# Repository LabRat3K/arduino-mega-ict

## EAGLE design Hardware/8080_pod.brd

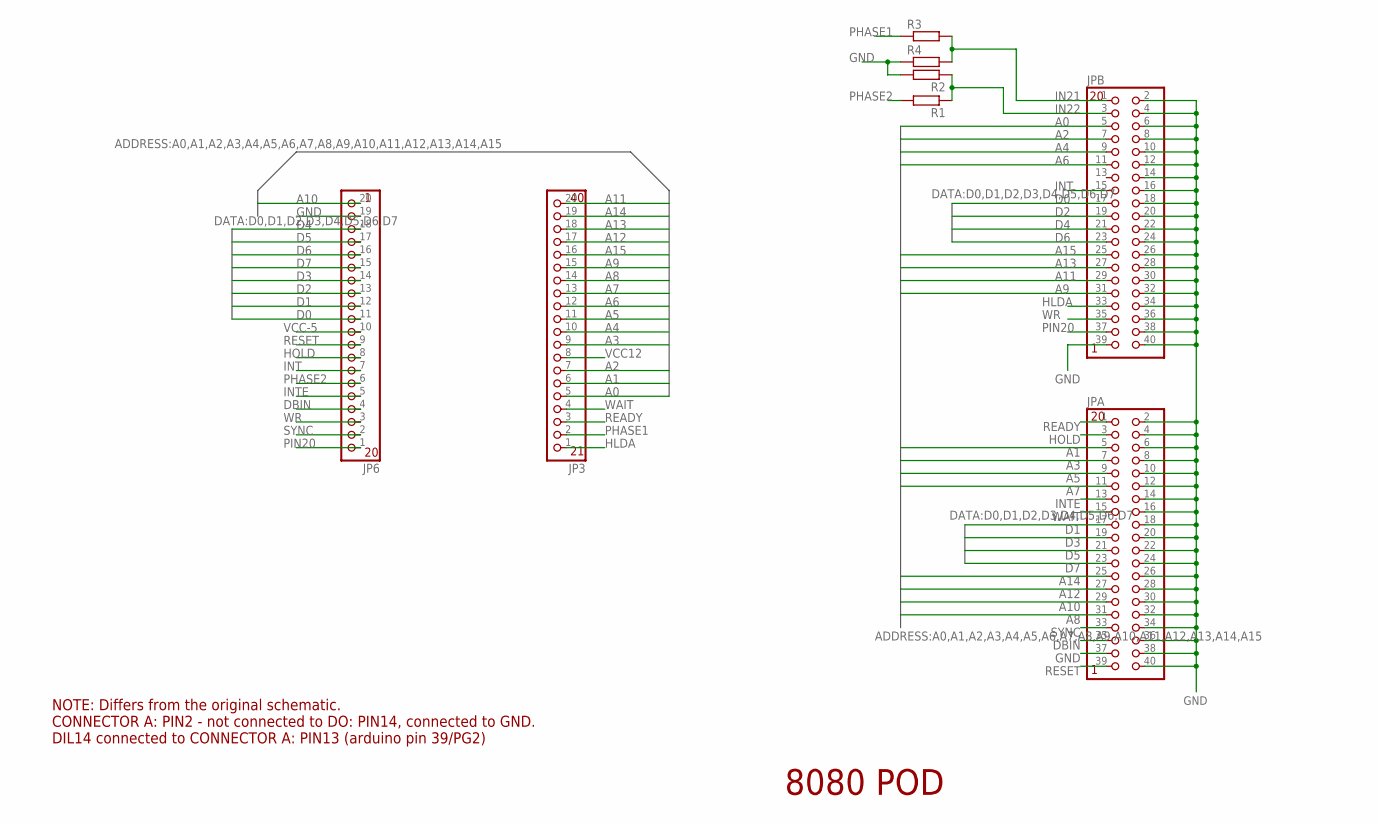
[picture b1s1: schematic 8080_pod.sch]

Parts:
JP3, JP6: PINHD-1X20-BIG; 1X20-BIG
JPA: PINHD-2X20-BIG; 2X20-BIG
JPB: PINHD-2X20-BIG; 2X20-BIG
R1, R2, R3, R4: R-EU_0207/10; 0207/10

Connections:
A0: JP3.5, JPB.5
A1: JP3.6, JPA.5
A2: JP3.7, JPB.7
A3: JP3.9, JPA.7
A4: JP3.10, JPB.9
A5: JP3.11, JPA.9
A6: JP3.12, JPB.11
A7: JP3.13, JPA.11
A8: JP3.14, JPA.31
A9: JP3.15, JPB.31
A10: JP6.20, JPA.29
A11: JP3.20, JPB.29
A12: JP3.17, JPA.27
A13: JP3.18, JPB.27
A14: JP3.19, JPA.25
A15: JP3.16, JPB.25
D0: JP6.11, JPB.17
D1: JP6.12, JPA.17
D2: JP6.13, JPB.19
D3: JP6.14, JPA.19
D4: JP6.18, JPB.21
D5: JP6.17, JPA.21
D6: JP6.16, JPB.23
D7: JP6.15, JPA.23
DBIN: JP6.4, JPA.35
GND: JP6.19, JPA.2, JPA.4, JPA.6, JPA.8, JPA.10, JPA.12, JPA.14, JPA.16, JPA.18, JPA.20, JPA.22, JPA.24, JPA.26, JPA.28, JPA.30, JPA.32, JPA.34, JPA.36, JPA.37, JPA.38, JPA.40, JPB.2, JPB.4, JPB.6, JPB.8, JPB.10, JPB.12, JPB.14, JPB.16, JPB.18, JPB.20, JPB.22, JPB.24, JPB.26, JPB.28, JPB.30, JPB.32, JPB.34, JPB.36, JPB.38, JPB.39, JPB.40, R2.2, R4.1
HLDA: JP3.1, JPB.33
HOLD: JP6.8, JPA.3
IN21: JPB.1, R3.2, R4.2
IN22: JPB.3, R1.1, R2.1
INT: JP6.7, JPB.15
INTE: JP6.5, JPA.13
PHASE1: JP3.2, R3.1
PHASE2: JP6.6, R1.2
PIN20: JP6.1, JPB.37
READY: JP3.3, JPA.1
RESET: JP6.9, JPA.39
SYNC: JP6.2, JPA.33
VCC12: JP3.8
VCC-5: JP6.10
WAIT: JP3.4, JPA.15
WR: JP6.3, JPB.35

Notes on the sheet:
8080 POD
NOTE: Differs from the original schematic. CONNECTOR A: PIN2 - not connected to DO: PIN14, connected to GND. DIL14 connected to CONNECTOR A: PIN13 (arduino pin 39/PG2)

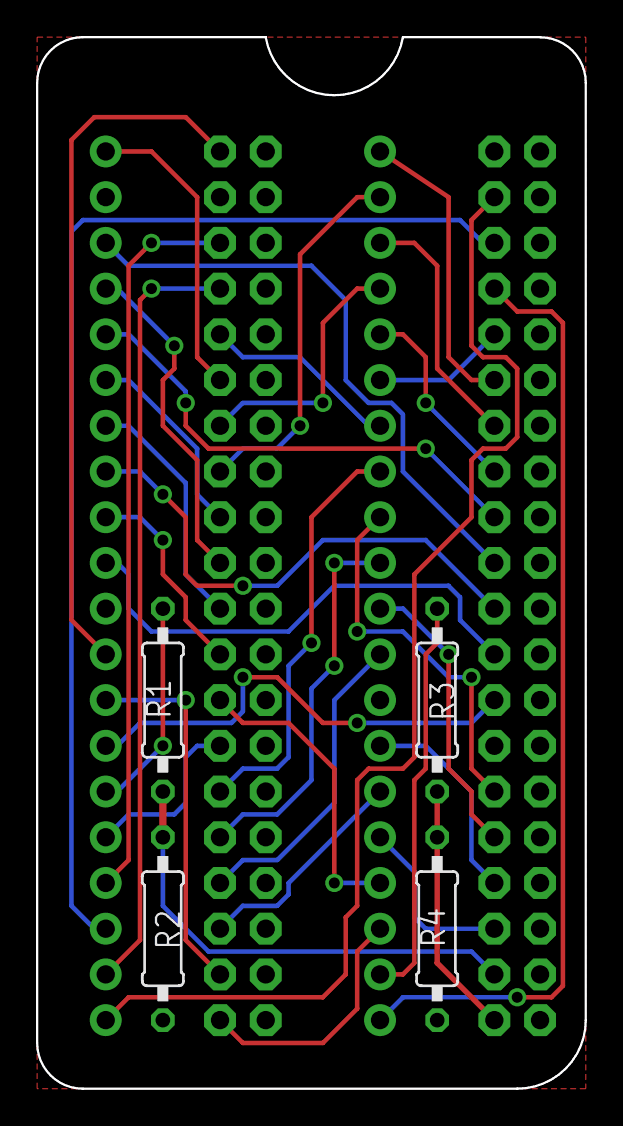
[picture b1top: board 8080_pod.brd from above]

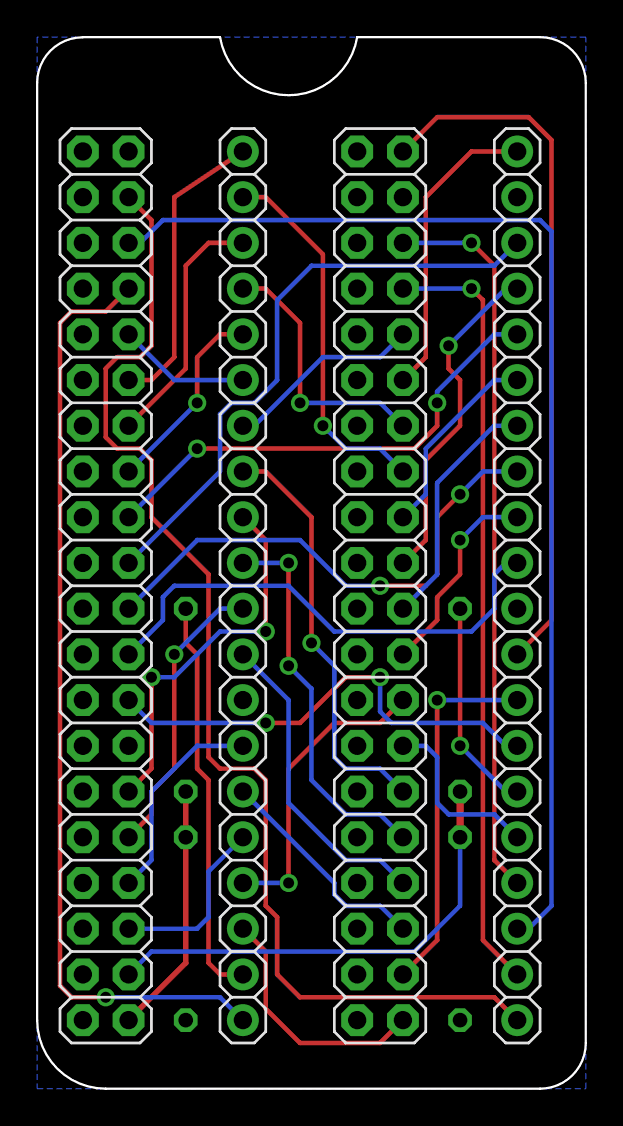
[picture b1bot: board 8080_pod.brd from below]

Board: 2 copper layers, 30.5 x 58.4 mm, 8 parts (4 on the bottom side), 40 nets.

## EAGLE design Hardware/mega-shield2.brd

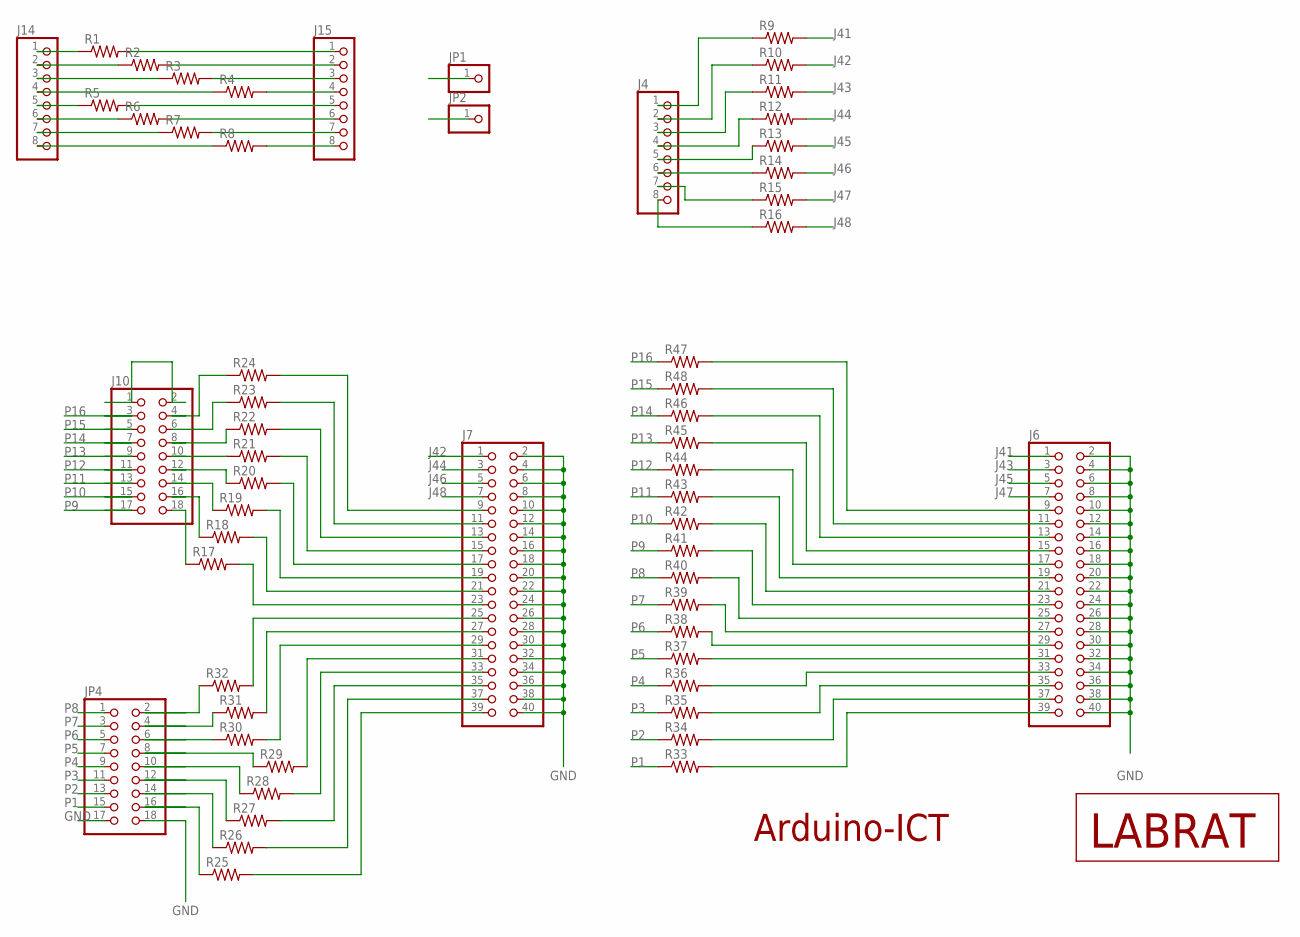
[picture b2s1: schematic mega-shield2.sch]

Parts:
J4, J14, J15: PINHD-1X8BIG; 1X08-BIG
J6, J7: PINHD-2X20; 2X20
J10: PINHD-2X9-BIG; 2X09-BIG
JP1, JP2: PINHD-1X1; 1X01
JP4: PINHD-2X9-BIG; 2X09-BIG
R1, R2, R3, R4, R5, R6, R7, R8, R9, R10, R11, R12, R13, R14, R15, R16, R17, R18, R19, R20, R21, R22, R23, R24, R25, R26, R27, R28, R29, R30, R31, R32, R33, R34, R35, R36, R37, R38, R39, R40, R41, R42, R43, R44, R45, R46, R47, R48: R-US_0204/5; 0204/5
U$1: LOGOLABRAT; LOGO

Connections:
GND: J6.2, J6.4, J6.6, J6.8, J6.10, J6.12, J6.14, J6.16, J6.18, J6.20, J6.22, J6.24, J6.26, J6.28, J6.30, J6.32, J6.34, J6.36, J6.38, J6.40, J7.2, J7.4, J7.6, J7.8, J7.10, J7.12, J7.14, J7.16, J7.18, J7.20, J7.22, J7.24, J7.26, J7.28, J7.30, J7.32, J7.34, J7.36, J7.38, J7.40, JP1.1, JP2.1, JP4.17, JP4.18
J41: J6.1, R9.2
J42: J7.1, R10.2
J43: J6.3, R11.2
J44: J7.3, R12.2
J45: J6.5, R13.2
J46: J7.5, R14.2
J47: J6.7, R15.2
J48: J7.7, R16.2
unnamed: J14.1, R1.1
unnamed: J15.1, R1.2
unnamed: J14.2, R2.1
unnamed: J14.3, R3.1
unnamed: J14.4, R4.1
unnamed: J14.5, R5.1
unnamed: J14.6, R6.1
unnamed: J14.7, R7.1
unnamed: J14.8, R8.1
unnamed: J15.2, R2.2
unnamed: J15.3, R3.2
unnamed: J15.4, R4.2
unnamed: J15.5, R5.2
unnamed: J15.6, R6.2
unnamed: J15.7, R7.2
unnamed: J15.8, R8.2
unnamed: JP4.16, R25.1
unnamed: J7.39, R25.2
unnamed: JP4.14, R26.1
unnamed: JP4.12, R27.1
unnamed: JP4.10, R28.1
unnamed: J7.37, R26.2
unnamed: J7.35, R27.2
unnamed: J7.33, R28.2
unnamed: JP4.8, R29.1
unnamed: JP4.6, R30.1
unnamed: JP4.4, R31.1
unnamed: JP4.2, R32.1
unnamed: J7.31, R29.2
unnamed: J7.29, R30.2
unnamed: J7.27, R31.2
unnamed: J7.25, R32.2
unnamed: J7.23, R17.2
unnamed: J7.21, R18.2
unnamed: J7.19, R19.2
unnamed: J7.17, R20.2
unnamed: J10.18, R17.1
unnamed: J10.16, R18.1
unnamed: J10.14, R19.1
unnamed: J10.12, R20.1
unnamed: J10.10, R21.1
unnamed: J10.8, R22.1
unnamed: J10.6, R23.1
unnamed: J10.4, R24.1
unnamed: J7.15, R21.2
unnamed: J7.13, R22.2
unnamed: J7.11, R23.2
unnamed: J7.9, R24.2
unnamed: J10.1, J10.2
unnamed: J4.8, R16.1
unnamed: J4.7, R15.1
unnamed: J4.6, R14.1
unnamed: J4.5, R13.1
unnamed: J4.4, R12.1
unnamed: J4.3, R11.1
unnamed: J4.2, R10.1
unnamed: J4.1, R9.1
unnamed: J6.39, R33.2
unnamed: J6.37, R34.2
unnamed: J6.35, R35.2
unnamed: J6.33, R36.2
unnamed: J6.31, R37.2
unnamed: J6.29, R38.2
unnamed: J6.27, R39.2
unnamed: J6.25, R40.2
unnamed: J6.23, R41.2
unnamed: J6.21, R42.2
unnamed: J6.19, R43.2
unnamed: J6.17, R44.2
unnamed: J6.15, R45.2
unnamed: J6.13, R46.2
unnamed: J6.11, R48.2
unnamed: J6.9, R47.2
P1: JP4.15, R33.1
P2: JP4.13, R34.1
P3: JP4.11, R35.1
P4: JP4.9, R36.1
P5: JP4.7, R37.1
P6: JP4.5, R38.1
P7: JP4.3, R39.1
P8: JP4.1, R40.1
P9: J10.17, R41.1
P10: J10.15, R42.1
P11: J10.13, R43.1
P12: J10.11, R44.1
P13: J10.9, R45.1
P14: J10.7, R46.1
P15: J10.5, R48.1
P16: J10.3, R47.1

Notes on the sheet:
Arduino-ICT

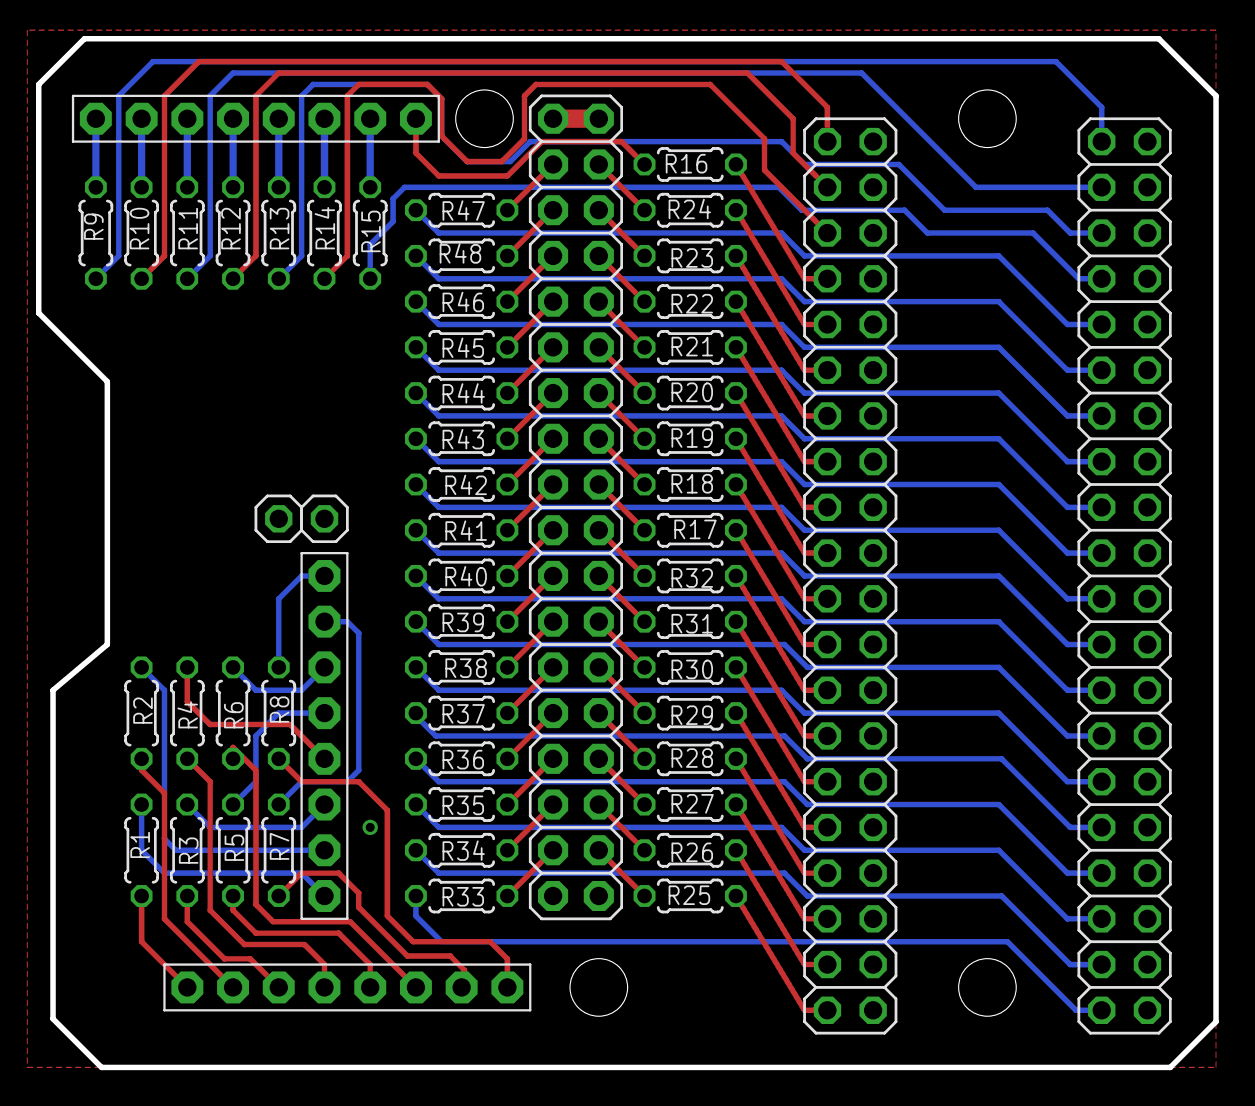
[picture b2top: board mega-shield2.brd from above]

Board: 2 copper layers, 65.4 x 57.1 mm, 58 parts (0 on the bottom side), 98 nets.

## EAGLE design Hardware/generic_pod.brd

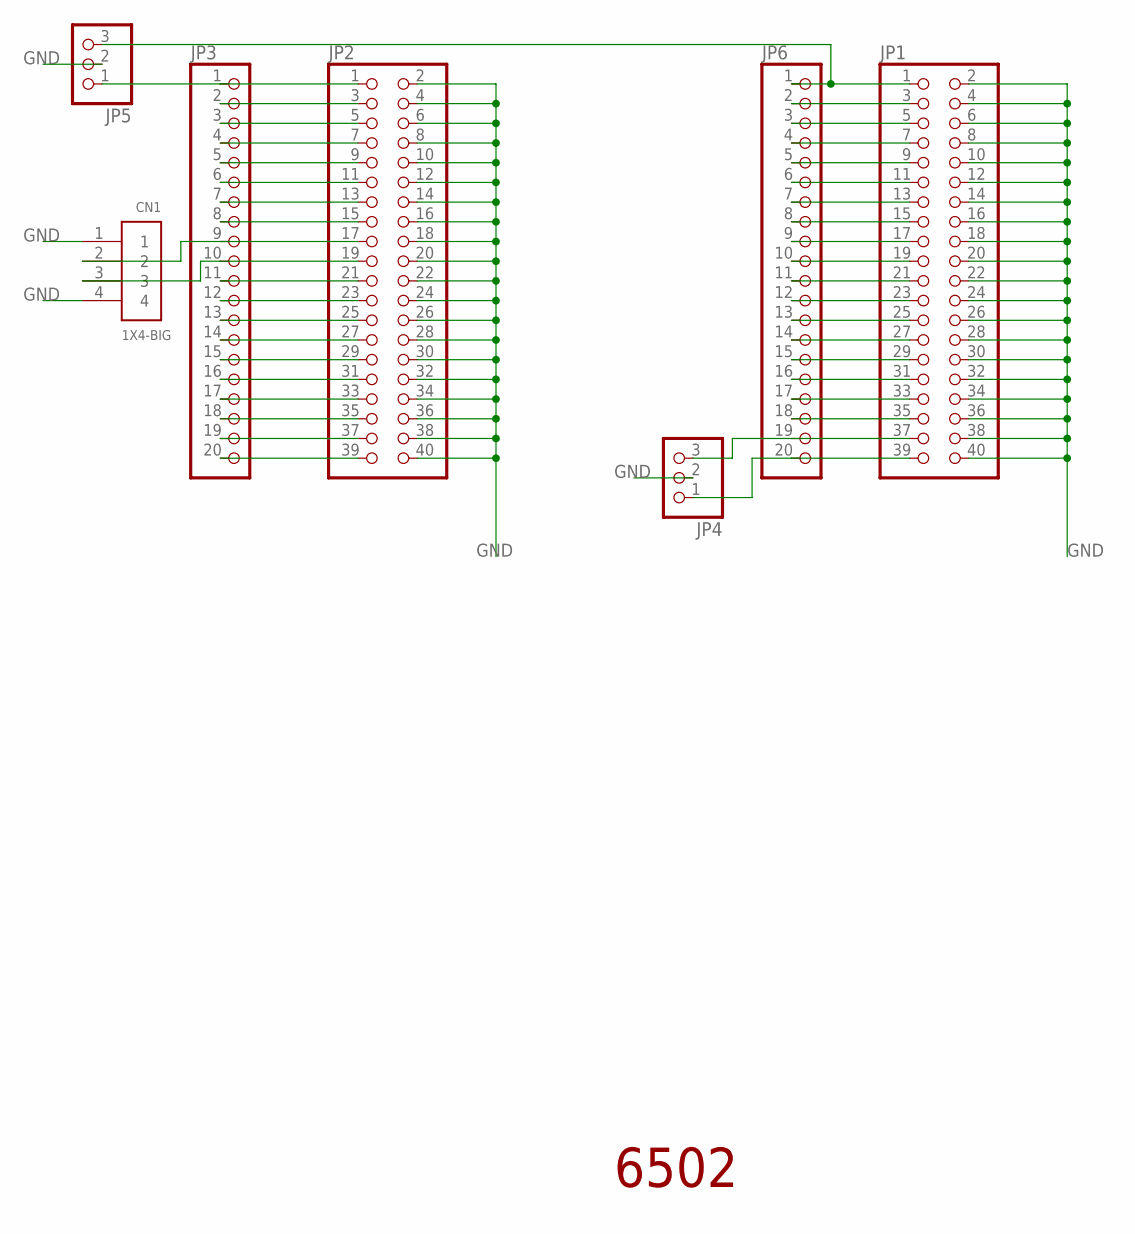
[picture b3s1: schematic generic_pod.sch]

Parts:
CN1: 1X4-BIG; 1X04-BIG
JP1, JP2: PINHD-2X20-BIG; 2X20-BIG
JP3, JP6: PINHD-1X20-BIG; 1X20-BIG
JP4, JP5: PINHD-1X3; 1X03

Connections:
GND: CN1.1, CN1.4, JP1.2, JP1.4, JP1.6, JP1.8, JP1.10, JP1.12, JP1.14, JP1.16, JP1.18, JP1.20, JP1.22, JP1.24, JP1.26, JP1.28, JP1.30, JP1.32, JP1.34, JP1.36, JP1.38, JP1.40, JP2.2, JP2.4, JP2.6, JP2.8, JP2.10, JP2.12, JP2.14, JP2.16, JP2.18, JP2.20, JP2.22, JP2.24, JP2.26, JP2.28, JP2.30, JP2.32, JP2.34, JP2.36, JP2.38, JP2.40, JP4.2, JP5.2
unnamed: JP2.1, JP3.1, JP5.1
unnamed: JP2.3, JP3.2
unnamed: JP2.5, JP3.3
unnamed: JP2.7, JP3.4
unnamed: JP2.9, JP3.5
unnamed: JP2.11, JP3.6
unnamed: JP2.13, JP3.7
unnamed: JP2.15, JP3.8
unnamed: CN1.2, JP2.17, JP3.9
unnamed: CN1.3, JP2.19, JP3.10
unnamed: JP2.21, JP3.11
unnamed: JP2.23, JP3.12
unnamed: JP2.25, JP3.13
unnamed: JP2.27, JP3.14
unnamed: JP2.29, JP3.15
unnamed: JP2.31, JP3.16
unnamed: JP2.33, JP3.17
unnamed: JP2.35, JP3.18
unnamed: JP2.37, JP3.19
unnamed: JP2.39, JP3.20
unnamed: JP1.1, JP5.3, JP6.1
unnamed: JP1.3, JP6.2
unnamed: JP1.5, JP6.3
unnamed: JP1.7, JP6.4
unnamed: JP1.9, JP6.5
unnamed: JP1.11, JP6.6
unnamed: JP1.13, JP6.7
unnamed: JP1.15, JP6.8
unnamed: JP1.17, JP6.9
unnamed: JP1.19, JP6.10
unnamed: JP1.21, JP6.11
unnamed: JP1.23, JP6.12
unnamed: JP1.25, JP6.13
unnamed: JP1.27, JP6.14
unnamed: JP1.29, JP6.15
unnamed: JP1.31, JP6.16
unnamed: JP1.33, JP6.17
unnamed: JP1.35, JP6.18
unnamed: JP1.37, JP4.3, JP6.19
unnamed: JP1.39, JP4.1, JP6.20

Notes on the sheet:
6502

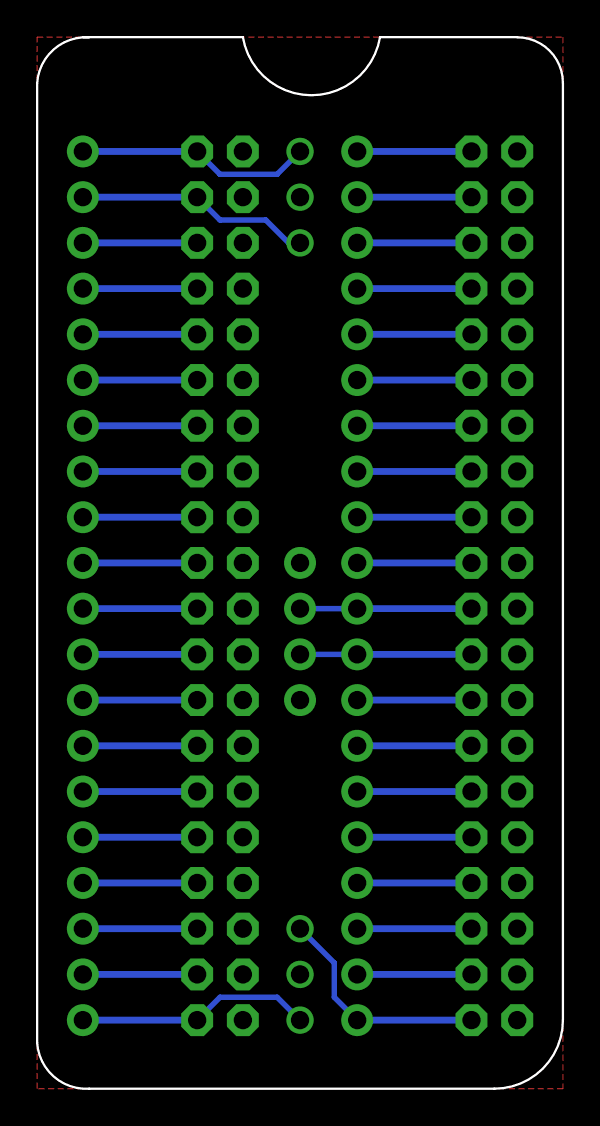
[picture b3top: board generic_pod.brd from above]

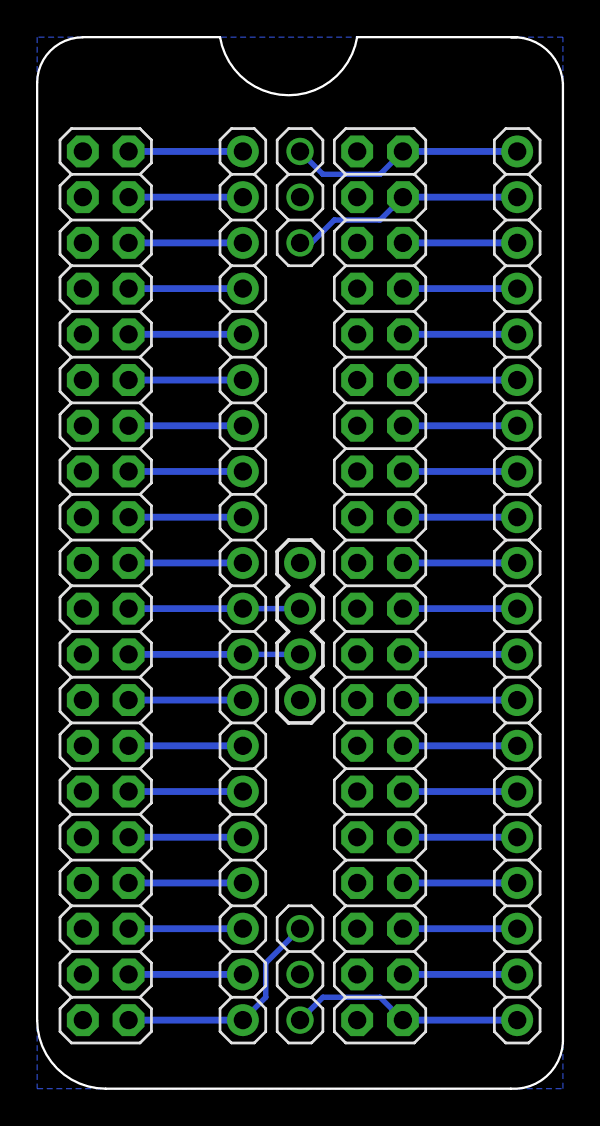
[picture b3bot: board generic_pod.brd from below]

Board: 2 copper layers, 29.2 x 58.4 mm, 7 parts (7 on the bottom side), 41 nets.

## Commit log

2021-01-23 Build option for GPIO based keypad vs DFR_Keypad
2021-01-23 Splash Screen update - learning to code
2021-01-24 Rework CONFIG menus to see values before they are SELECTED. Add SELECT GAME and EXIT options.
2021-01-24 Fix issue or REPEAT timeout impacting CONFIG options.
2021-01-24 Update CONFIG options to use existing SUBMENU code. UI changes to show changes as they are made, versus SELECT to commit changes
2021-01-26 Keypad update: Fix incorrect pin assignment
2021-01-26 Update delay in keypad_test to only apply to visible keypresses
2021-02-16 Restructure the GPIO driver to be compatible with DFR_Key handler.
2021-02-16 Fix merge
2021-03-13 Add HW PCB files (Cadsoft Eagle) to repo
2021-03-15 Add Gerbers, and tweak file permissions
2026-05-03 Fix timing values, and menu up/down
